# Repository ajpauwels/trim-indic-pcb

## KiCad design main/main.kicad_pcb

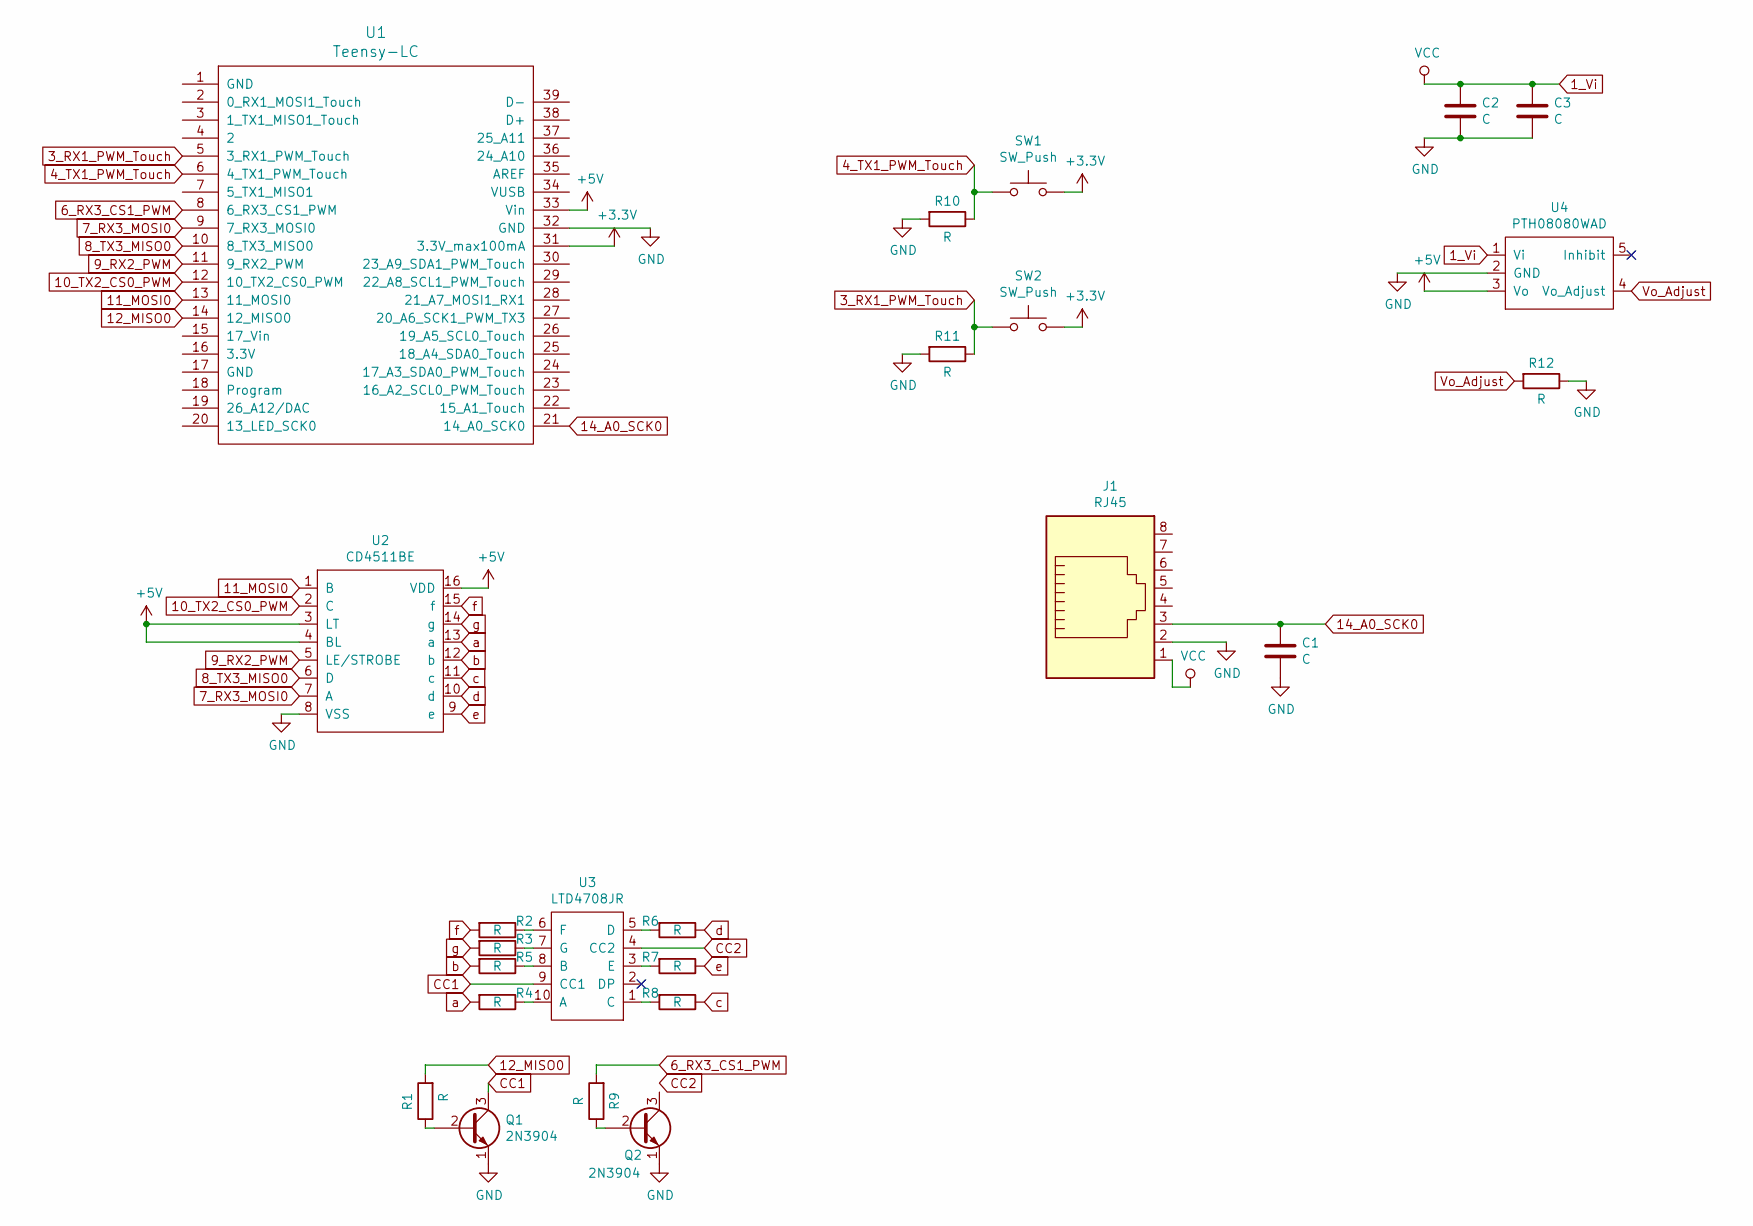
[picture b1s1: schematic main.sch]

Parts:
C1, C2, C3: C; C_Disc_D16.0mm_W5.0mm_P10.00mm
J1: RJ45; RJ45_Amphenol_54602-x08_Horizontal
Q1, Q2: 2N3904; TO-92_Inline
R1, R2, R3, R4, R5, R6, R7, R8, R9, R10, R11, R12: R; R_Axial_DIN0207_L6.3mm_D2.5mm_P7.62mm_Horizontal
SW1, SW2: SW_Push; SW_PUSH_6mm_H5mm
U1: Teensy-LC; Teensy30_31_32_LC
U2: CD4511BE; DIP-16_W7.62mm
U3: LTD4708JR
U4: PTH08080WAD

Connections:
3_RX1_PWM_Touch: R11.1, SW2.1, U1.5 (3_RX1_PWM_Touch)
4_TX1_PWM_Touch: R10.1, SW1.1, U1.6 (4_TX1_PWM_Touch)
6_RX3_CS1_PWM: R9.2, U1.8 (6_RX3_CS1_PWM)
7_RX3_MOSI0: U1.9 (7_RX3_MOSI0), U2.7 (A)
8_TX3_MISO0: U1.10 (8_TX3_MISO0), U2.6 (D)
9_RX2_PWM: U1.11 (9_RX2_PWM), U2.5 (LE/STROBE)
10_TX2_CS0_PWM: U1.12 (10_TX2_CS0_PWM), U2.2 (C)
11_MOSI0: U1.13 (11_MOSI0), U2.1 (B)
12_MISO0: R1.2, U1.14 (12_MISO0)
14_A0_SCK0: C1.1, J1.3, U1.21 (14_A0_SCK0)
+3V3: SW1.2, SW2.2, U1.31 (3.3V_max100mA)
+5V: U1.33 (Vin), U2.3 (LT), U2.4 (BL), U2.16 (VDD), U4.3 (Vo)
GND: C1.2, C2.2, C3.2, J1.2, Q1.1 (E), Q2.1 (E), R10.2, R11.2, R12.1, U1.32 (GND), U2.8 (VSS), U4.2 (GND)
unnamed: Q1.2 (B), R1.1
unnamed: Q1.3 (C), U3.9 (CC1)
unnamed: Q2.2 (B), R9.1
unnamed: Q2.3 (C), U3.4 (CC2)
unnamed: R2.1, U3.6 (F)
unnamed: R3.1, U3.7 (G)
unnamed: R4.1, U3.10 (A)
unnamed: R5.1, U3.8 (B)
unnamed: R6.2, U3.5 (D)
unnamed: R7.2, U3.3 (E)
unnamed: R8.2, U3.1 (C)
unnamed: R12.2, U4.4 (Vo_Adjust)
VCC: C2.1, C3.1, J1.1, U4.1 (Vi)
a: R4.2, U2.13 (a)
b: R5.2, U2.12 (b)
c: R8.1, U2.11 (c)
d: R6.1, U2.10 (d)
e: R7.1, U2.9 (e)
f: R2.2, U2.15 (f)
g: R3.2, U2.14 (g)

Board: 2 copper layers, 24 parts (0 on the bottom side), 33 nets, no tracks yet.

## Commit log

2018-12-17 Add all kicad files
